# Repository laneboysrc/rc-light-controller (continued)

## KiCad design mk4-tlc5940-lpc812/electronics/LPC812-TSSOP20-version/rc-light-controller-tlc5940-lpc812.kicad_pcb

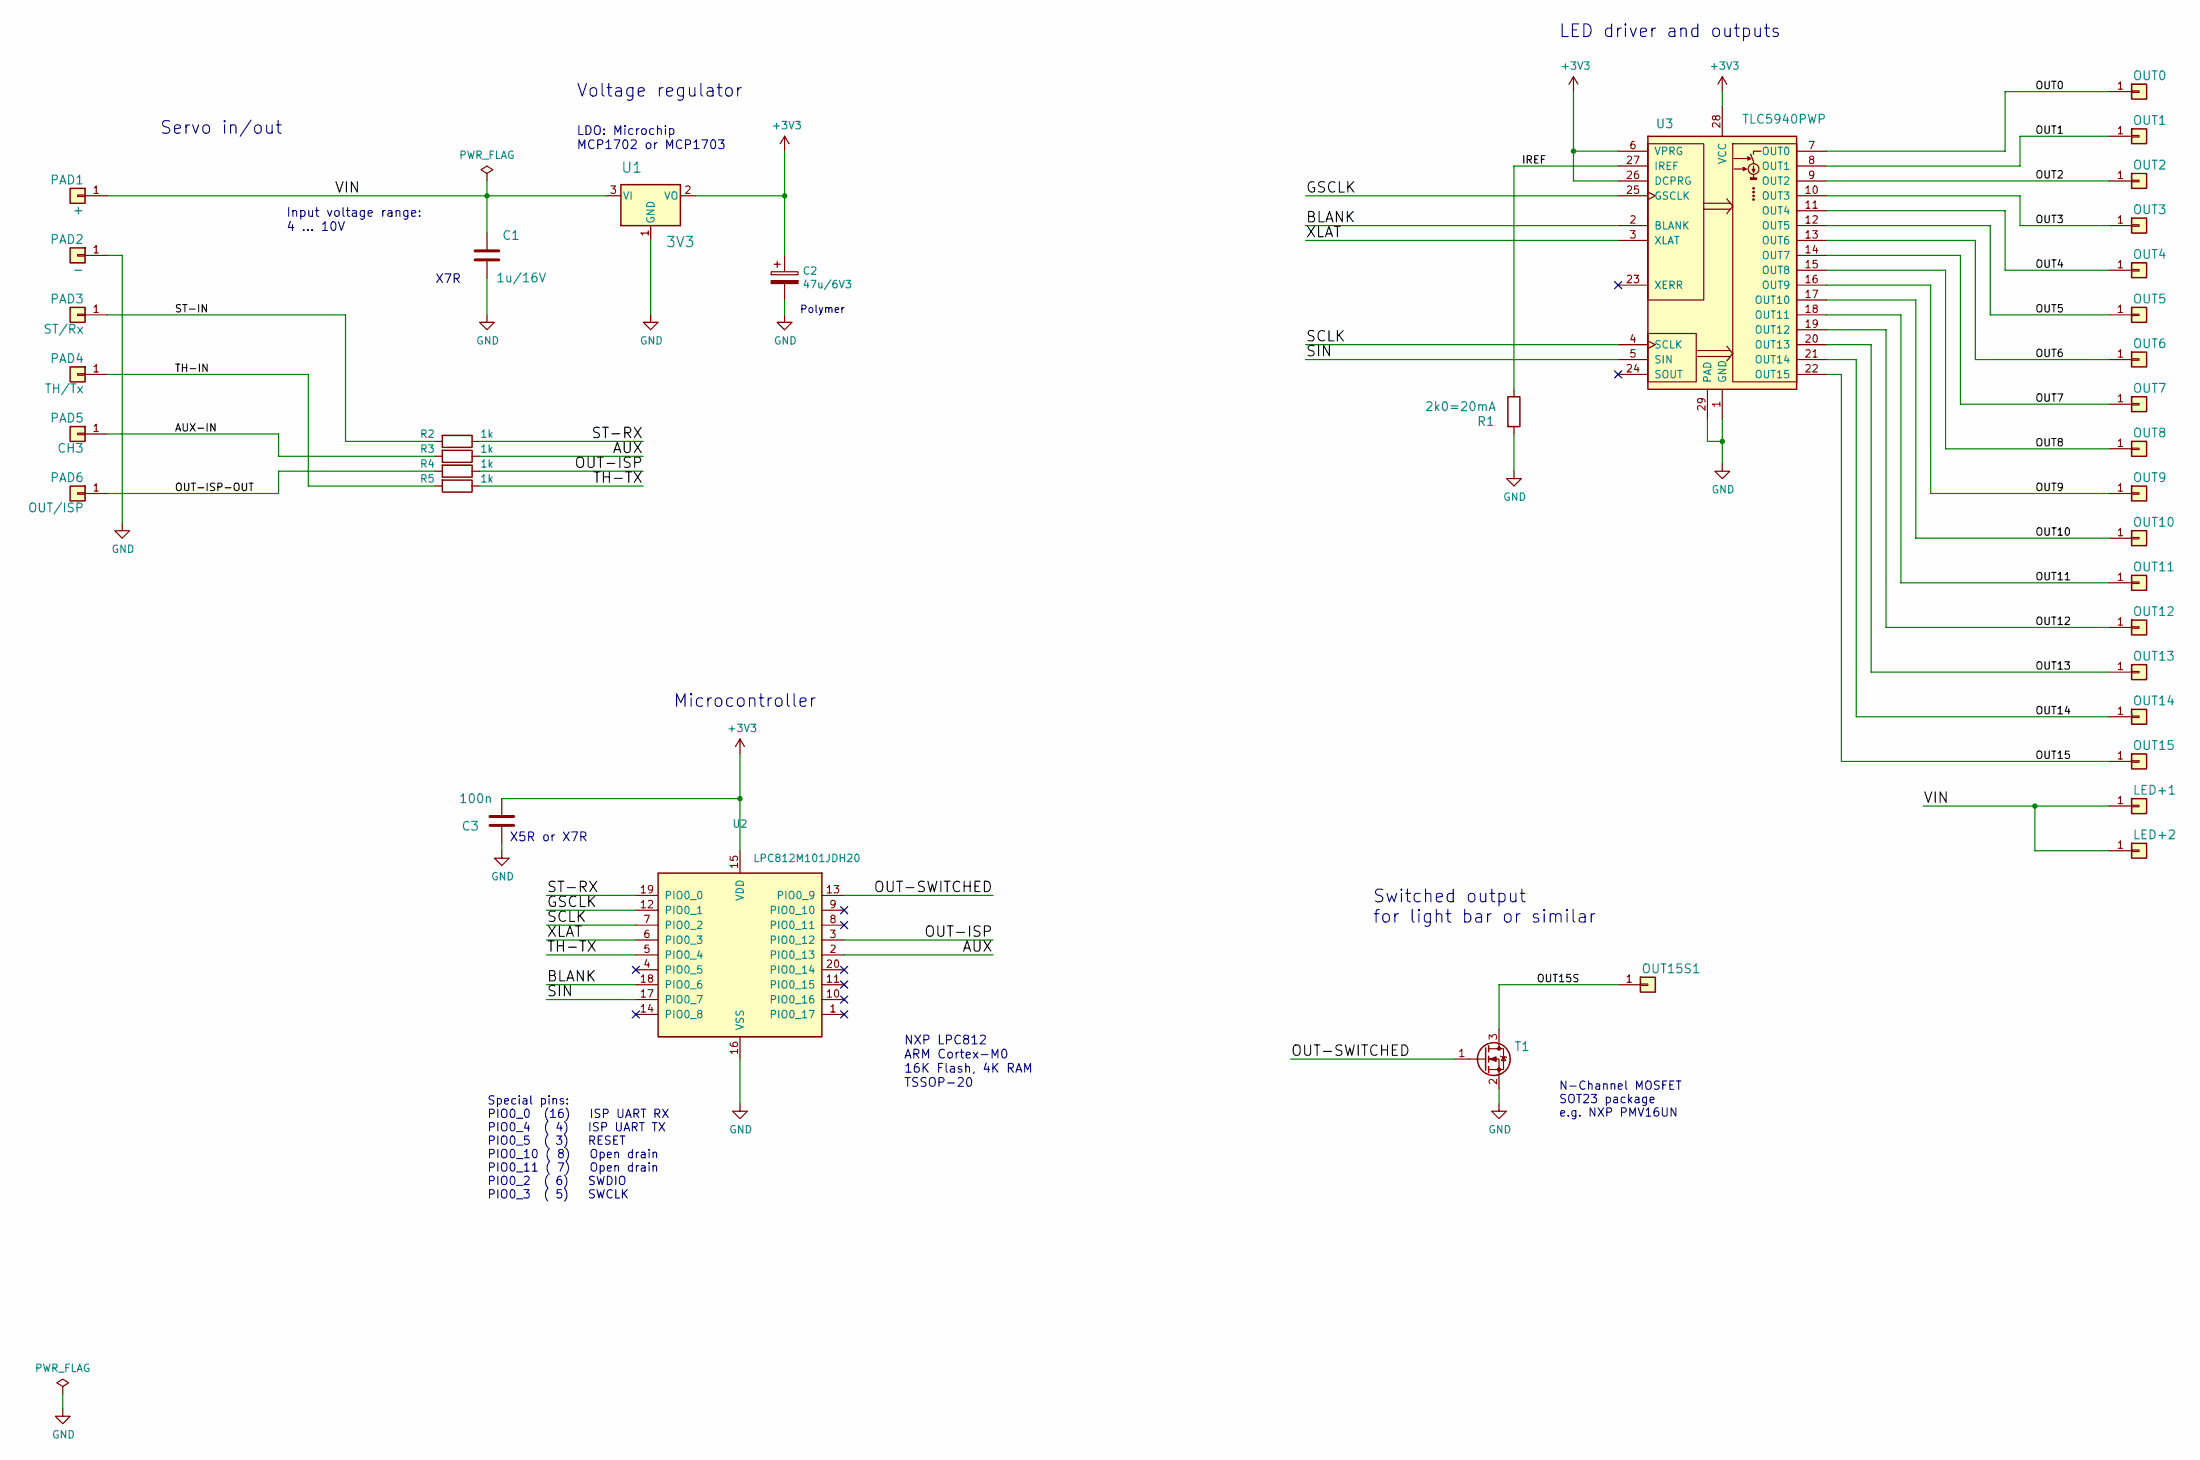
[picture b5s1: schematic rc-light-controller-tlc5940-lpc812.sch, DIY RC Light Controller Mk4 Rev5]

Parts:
C1: 1u/16V; C_0805_2012Metric
C2: 47u/6V3; C_0805_2012Metric
C3: 100n; C_0603_1608Metric
LED+1, LED+2: SMD50X100
OUT0, OUT1, OUT2, OUT3, OUT4, OUT5, OUT6, OUT7, OUT8, OUT9, OUT10, OUT11, OUT12, OUT13, OUT14, OUT15, OUT15S1: SMD50X100
PAD1: +; SMD80X120
PAD2: -; SMD80X120
PAD3: ST/Rx; SMD80X120
PAD4: TH/Tx; SMD80X120
PAD5: CH3; SMD80X120
PAD6: OUT/ISP; SMD80X120
R1: 2k0=20mA; R_0603_1608Metric
R2, R3, R4, R5: 1k; R_0603_1608Metric
T1: NMOSSOT23; SOT-23
U1: 3V3; SOT-23W
U2: LPC812M101JDH20; TSSOP-20_4.4x6.5mm_P0.65mm
U3: TLC5940PWP; SOP65P640X120-29N

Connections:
+3V3: C2.1, C3.2, U1.2 (VO), U2.15 (VDD), U3.6 (VPRG), U3.26 (DCPRG), U3.28 (VCC)
/AUX: R3.1, U2.2 (PIO0_13)
/AUX-IN: PAD5.1, R3.2
/BLANK: U2.18 (PIO0_6), U3.2 (BLANK)
/GSCLK: U2.12 (PIO0_1), U3.25 (GSCLK)
/IREF: R1.1, U3.27 (IREF)
/OUT0: OUT0.1, U3.7 (OUT0)
/OUT1: OUT1.1, U3.8 (OUT1)
/OUT2: OUT2.1, U3.9 (OUT2)
/OUT3: OUT3.1, U3.10 (OUT3)
/OUT4: OUT4.1, U3.11 (OUT4)
/OUT5: OUT5.1, U3.12 (OUT5)
/OUT6: OUT6.1, U3.13 (OUT6)
/OUT7: OUT7.1, U3.14 (OUT7)
/OUT8: OUT8.1, U3.15 (OUT8)
/OUT9: OUT9.1, U3.16 (OUT9)
/OUT10: OUT10.1, U3.17 (OUT10)
/OUT11: OUT11.1, U3.18 (OUT11)
/OUT12: OUT12.1, U3.19 (OUT12)
/OUT13: OUT13.1, U3.20 (OUT13)
/OUT14: OUT14.1, U3.21 (OUT14)
/OUT15: OUT15.1, U3.22 (OUT15)
/OUT15S: OUT15S1.1, T1.3 (D)
/OUT-ISP: R4.1, U2.3 (PIO0_12)
/OUT-ISP-OUT: PAD6.1, R4.2
/OUT-SWITCHED: T1.1 (G), U2.13 (PIO0_9)
/SCLK: U2.7 (PIO0_2), U3.4 (SCLK)
/SIN: U2.17 (PIO0_7), U3.5 (SIN)
/ST-IN: PAD3.1, R2.2
/ST-RX: R2.1, U2.19 (PIO0_0)
/TH-IN: PAD4.1, R5.2
/TH-TX: R5.1, U2.5 (PIO0_4)
/VIN: C1.1, LED+1.1, LED+2.1, PAD1.1, U1.3 (VI)
/XLAT: U2.6 (PIO0_3), U3.3 (XLAT)
GND: C1.2, C2.2, C3.1, PAD2.1, R1.2, T1.2 (S), U1.1 (GND), U2.16 (VSS), U3.1 (GND), U3.29 (PAD)

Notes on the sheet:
Special pins: PIO0_0 (16) ISP UART RX PIO0_4 ( 4) ISP UART TX PIO0_5 ( 3) RESET PIO0_10 ( 8) Open drain PIO0_11 ( 7) Open drain PIO0_2 ( 6) SWDIO PIO0_3 ( 5) SWCLK
Servo in/out
LED driver and outputs
Voltage regulator
Microcontroller
X7R
Input voltage range: 4 ... 10V
LDO: Microchip MCP1702 or MCP1703
X5R or X7R
NXP LPC812 ARM Cortex-M0 16K Flash, 4K RAM TSSOP-20
Switched output for light bar or similar
N-Channel MOSFET SOT23 package e.g. NXP PMV16UN
Polymer

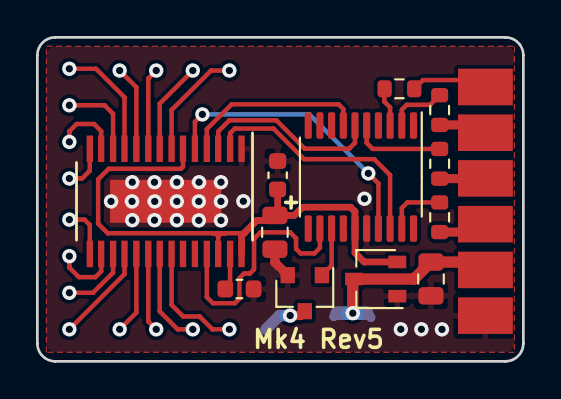
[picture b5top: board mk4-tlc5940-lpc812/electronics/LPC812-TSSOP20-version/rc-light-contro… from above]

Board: 2 copper layers, 27.0 x 18.0 mm, 37 parts (0 on the bottom side), 35 nets.

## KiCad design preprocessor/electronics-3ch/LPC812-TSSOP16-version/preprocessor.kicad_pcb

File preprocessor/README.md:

# Pre-processor

The pre-processor converts steering, throttle and AUX/CH3 signals into a single wire serial signal. By mounting the pre-processor near the receiver in the car chassis, you only need to run a standard servo extension cable to the light controller in the body shell.

This makes it very convenient when removing the body shell from the chassis: only one cable needs to be unplugged.

The pre-processor PCB also acts as "Y-cable" for steering and throttle. Use short male-to-male servo extensions to connect the pre-processor to your receiver, and plug the servo and ESC into the two extra ports on the pre-processor.

A [wiring diagram](../doc/preprocessor-wiring-diagram.pdf) explains how to connect the pre-processor, the light controller and the other electronics components in an RC car together.

The firmware for the pre-processor is the same as for the [MK4 variant](../mk4-tlc5940-lpc812/), you just have to utilize the MK4 configurator tool to generate a pre-processor firmware.

If the baud rate is configured to 38400, the pre-processor is also compatible with the MK2 and MK3 variants.

The PCB and schematics design was done in [KiCad EDA](http://kicad-pcb.org/)

3-channel Pre-Processor: [electronics-3ch/](electronics-3ch/)

5-channel Pre-Processor: [electronics-5ch/](electronics-5ch/)

5-channel Pre-Processor/switching light controller combination (4 switched LED outputs): [electronics-5ch-switching/](electronics-5ch-switching/)

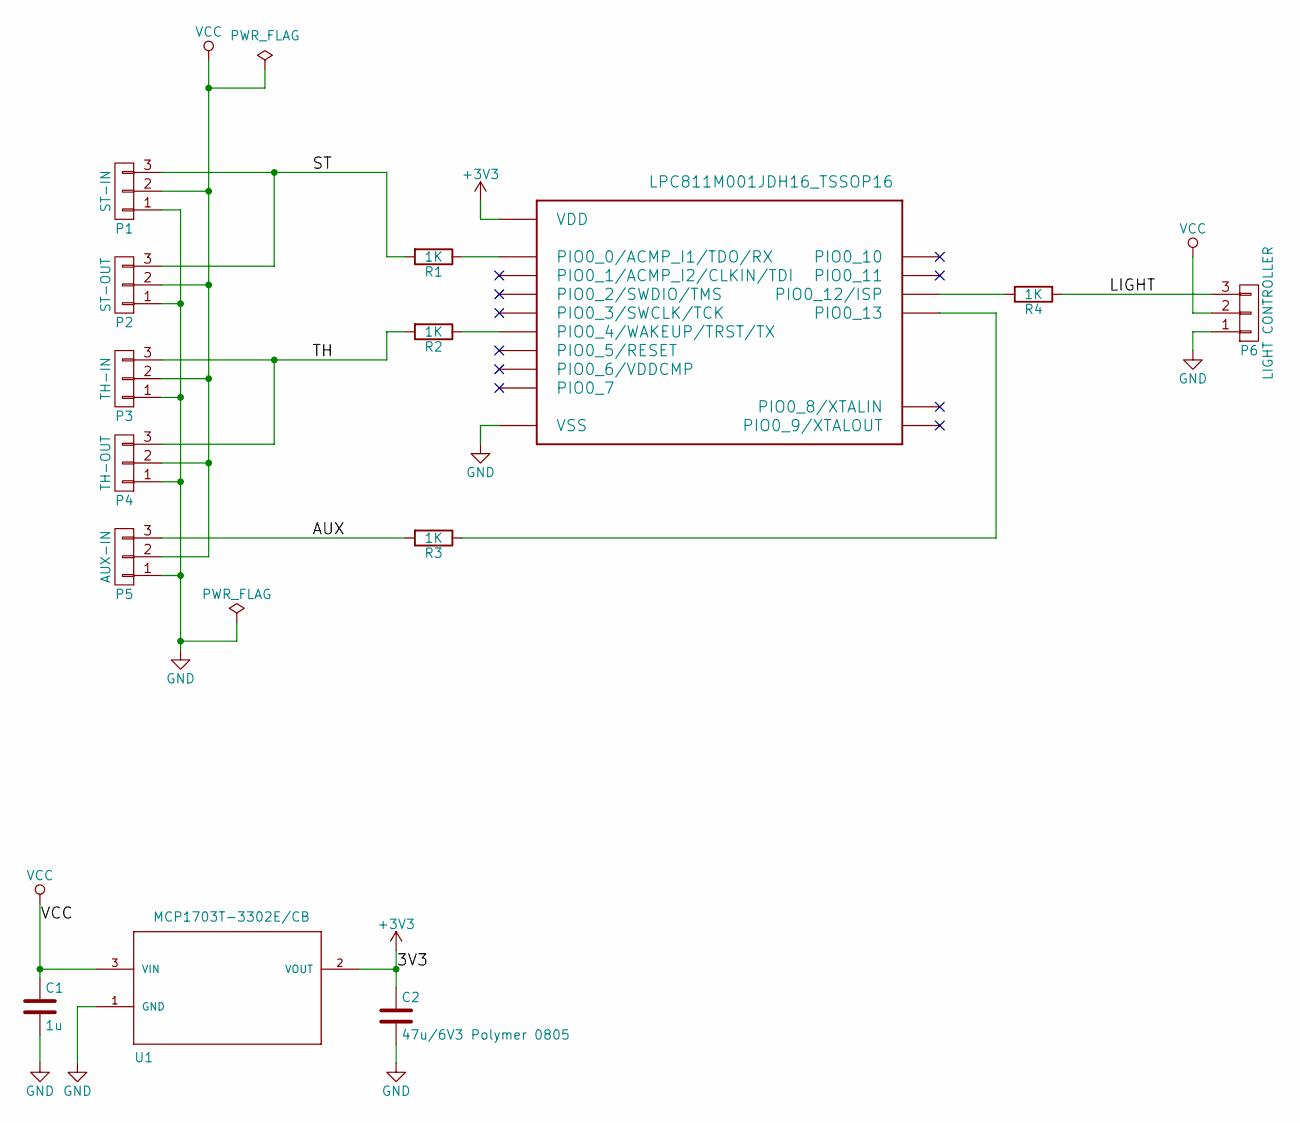
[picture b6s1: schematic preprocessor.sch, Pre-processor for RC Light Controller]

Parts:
C1: 1u; C_0805_2012Metric_Pad1.15x1.40mm_HandSolder
C2: 47u/6V3 Polymer 0805; C_0805_2012Metric_Pad1.15x1.40mm_HandSolder
P1: ST-IN; Pin_Header_Straight_1x03_Pitch2.54mm
P2: ST-OUT; Pin_Header_Straight_1x03_Pitch2.54mm
P3: TH-IN; Pin_Header_Straight_1x03_Pitch2.54mm
P4: TH-OUT; Pin_Header_Straight_1x03_Pitch2.54mm
P5: AUX-IN; Pin_Header_Straight_1x03_Pitch2.54mm
P6: LIGHT CONTROLLER; Pin_Header_Straight_1x03_Pitch2.54mm
R1, R2, R3, R4: 1K; R_0603_1608Metric_Pad1.05x0.95mm_HandSolder
U1: MCP1703T-3302E/CB; SOT-23W_Handsoldering
U2: LPC811M001JDH16_TSSOP16; TSSOP-16_4.4x5mm_P0.65mm

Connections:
+3V3: C2.1, U1.2 (VOUT), U2.12 (VDD)
/AUX: P5.3, R3.2
/LIGHT: P6.3, R4.1
/ST: P1.3, P2.3, R1.2
/TH: P3.3, P4.3, R2.2
GND: C1.2, C2.2, P1.1, P2.1, P3.1, P4.1, P5.1, P6.1, U1.1 (GND), U2.13 (VSS)
unnamed: R1.1, U2.16 (PIO0_0/ACMP_I1/TDO/RX)
unnamed: R2.1, U2.4 (PIO0_4/WAKEUP/TRST/TX)
unnamed: R3.1, U2.1 (PIO0_13)
unnamed: R4.2, U2.2 (PIO0_12/ISP)
VCC: C1.1, P1.2, P2.2, P3.2, P4.2, P5.2, P6.2, U1.3 (VIN)

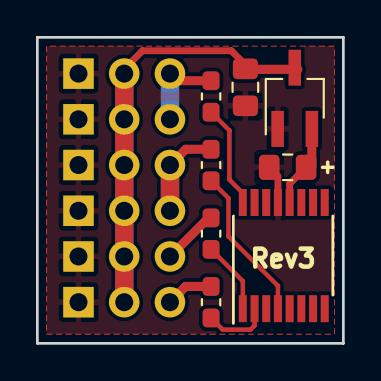
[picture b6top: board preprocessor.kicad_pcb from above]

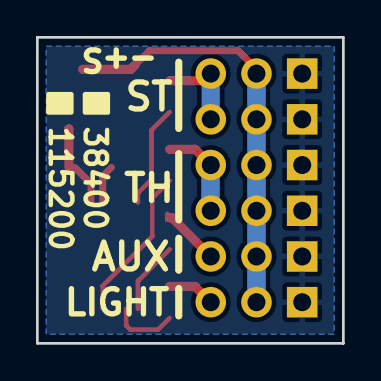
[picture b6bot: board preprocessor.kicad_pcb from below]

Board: 2 copper layers, 17.0 x 17.0 mm, 14 parts (6 on the bottom side), 11 nets.

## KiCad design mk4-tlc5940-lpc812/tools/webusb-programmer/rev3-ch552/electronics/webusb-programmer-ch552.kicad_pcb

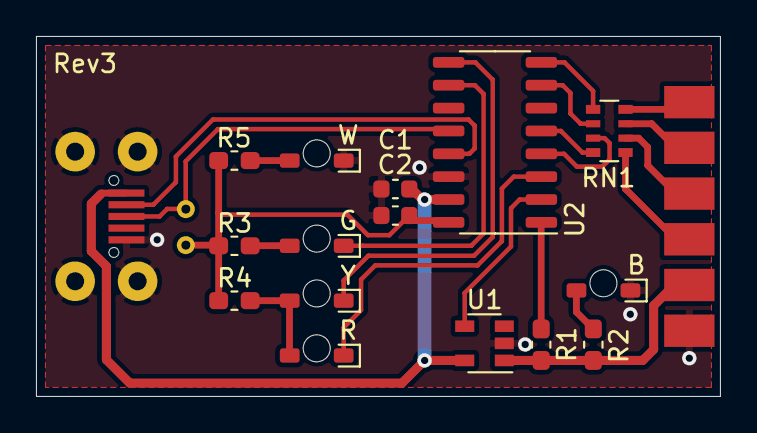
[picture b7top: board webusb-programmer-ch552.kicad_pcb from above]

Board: 2 copper layers, 38.0 x 20.0 mm, 19 parts (0 on the bottom side), 23 nets.

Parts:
C1: 1u; C_0603_1608Metric
C2: 100n; C_0603_1608Metric
D1: B; LED_1204_side_mout
D2: G; LED_1204_side_mout
D3: Y; LED_1204_side_mout
D4: R; LED_1204_side_mout
D5: W; LED_1204_side_mout
J1: Light Controller; PinHeader_1x06_P2.54mm_Flat
J2: USB_B_Micro; Mirco_USB_Type_B_LCSC_C40943
R1: 100; R_0603_1608Metric_Pad1.05x0.95mm_HandSolder
R2, R5: 1k8; R_0603_1608Metric_Pad1.05x0.95mm_HandSolder
R3: 180; R_0603_1608Metric_Pad1.05x0.95mm_HandSolder
R4: 1k2; R_0603_1608Metric_Pad1.05x0.95mm_HandSolder
RN1: 1k; R_Array_Convex_4x0603
TP1, TP2: TestPoint_THTPad_1.0x1.0mm_Drill0.5mm_nosilk
U1: STMPS2141STR; SOT-23-5
U2: CH552G; SO-16_3.9x9.9mm_P1.27mm

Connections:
+3V3: C2.1, R3.1, R4.1, R5.1, TP1.1, U2.16
+5V: C1.1, J2.1, U1.5, U2.15
/BUSY: D3.1, U2.9
/CH3: RN1.2, U2.7
/EN: U1.4, U2.2
/ERROR: D4.1, U2.3
/ISP: RN1.1, U2.8
/OK: D2.1, U2.10
/RX: RN1.3, U2.4
/SHORT: R1.2, U2.1
/TX: RN1.4, U2.5
/USB-DM: J2.2, U2.13
/USB-DP: J2.3, TP2.1, U2.12
/VLIGHT: J1.2, R1.1, R2.1, U1.1
GND: C1.2, C2.2, D1.1, D5.1, J1.1, J2.5, J2.6, U1.2, U2.14
unnamed: D1.2, R2.2
unnamed: D2.2, R3.2
unnamed: D3.2, D4.2, R4.2
unnamed: D5.2, R5.2
unnamed: J1.3, RN1.5
unnamed: J1.4, RN1.6
unnamed: J1.5, RN1.7
unnamed: J1.6, RN1.8

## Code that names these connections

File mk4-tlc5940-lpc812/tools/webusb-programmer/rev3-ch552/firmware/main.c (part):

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
#define GPIO_ADDRESS_SHORT (P3_ADDR)
#define GPIO_PIN_SHORT (2)
__sbit __at(GPIO_ADDRESS_SHORT | GPIO_PIN_SHORT) PIN_SHORT;

#define GPIO_ADDRESS_POWER (P1_ADDR)
#define GPIO_PIN_POWER (4)
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
#define GPIO_ADDRESS_ISP (P3_ADDR)
#define GPIO_PIN_ISP (0)
__sbit __at(GPIO_ADDRESS_ISP | GPIO_PIN_ISP) PIN_ISP;


// WebUSB programmer commands received via EP0 Vendor specific request
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
    // Watchdog expired: turn the power to the light controller off
    PIN_POWER = 1;
    PIN_SHORT = 0;

    // Turn the LEDs off
    LED_OK = LED_OFF;
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    LED_ERROR = LED_OFF;

    // Switch the UART TX and RX to GPIO output and set it to low, so that
    // we don't power the light controller via the ST/RX pin!
    U1REN = 0;
    TXD1 = 0;
    RXD1 = 0;
    PIN_ISP = 0;
    PIN_CH3 = 0;
}

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{
    switch (value) {
        case CMD_DUT_POWER_ON:
            PIN_SHORT = 1;
            PIN_POWER = 0;

            // Switch the TX and RX back to UART
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            PIN_POWER = 1;

            // Switch the UART TX and RX to GPIO output  and set it to low, so that
            // we don't power the light controller via the ST/RX pin!
            U1REN = 0;
            TXD1 = 0;
            RXD1 = 0;

            PIN_SHORT = 0;
            break;

        case CMD_LED_OK_ON:
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            break;

        case CMD_OUT_ISP_LOW:
            PIN_ISP = 0;
            P3_DIR_PU |= (1 << GPIO_PIN_ISP);   // Open drain output with pull-up
            break;

        case CMD_OUT_ISP_HIGH:
            PIN_ISP = 1;
            P3_DIR_PU |= (1 << GPIO_PIN_ISP);   // Open drain output with pull-up
            break;

        case CMD_OUT_ISP_TRISTATE:
            PIN_ISP = 1;
            P3_DIR_PU &= ~(1 << GPIO_PIN_ISP);  // High-impedance input mode
            break;

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    LED_ERROR = LED_OFF;

    PIN_POWER = 1;
    PIN_SHORT = 0;

    // Switch all light controller pins including UART TX and RX to low, so
    // that we don't power the light controller via the IO pins!
    PIN_ISP = 0;
    PIN_CH3 = 0;
    TXD1 = 0;
    RXD1 = 0;
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    // the ESD protection diodes of the light controller MCU -- which should
    // be fine.
    //
    // On a related note, we use the CH552 GPIO directly to short the light
    // controller power supply when off (to discharge the capacitors in the
    // light controller).
    //
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
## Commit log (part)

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2021-05-01 Fix new values when loading old configurations
2021-05-01 Make all example configurations work on latest configurator
    Main issue was labels being called "hazard", which is now
    a built-in variable by default
2021-05-08 Add updated user manual
    - New WebUSB Rev3 photo
    - Move driver info for USB-to-Serial to programming chapter
    - Add "which LEDs" info
2021-05-08 Update TODO
2021-05-09 Add product and LANE Boys RC label
2021-05-09 Rename pre-processor folders
    Instead of multi-aux, we call them 5ch as in the documentation.
    Also stream-line the folder structure of the 3ch and 5ch PP.
2021-05-09 Add 832 label
2021-05-09 Streamline gerber filenames and add schematics PDF everywhere
2021-05-10 Make ground flood go underneath LPC832
2021-05-11 Fix import of old .HEX files
2021-05-12 Add Gerber for LPC832 variants
2021-05-13 Show MCU part number in programming diagnostics
2021-05-13 Add light program that decodes multi-clicks on AUX2
2021-05-13 Improve README
2021-05-15 Adjust cut-out for the case
2021-05-20 Add "upper row is LED+" notice for Mk4P and Mk4S
2021-05-21 Fix 5ch-PP AUX2 for LPC832 variant
2021-05-22 Add German manual for 5ch-PP-S
2021-05-24 Fix PINENABLE for both LPC812 and LPC832
    v39 fixed LPC812, but 832-based Mk4P was no longer working because
    SWD pins are enabled after reset!
2021-05-24 Fix PINENABLE for LPC832l firmware v40
2021-05-26 Add light program that enables reversing lights only when main lights are on
2021-06-12 Web app for the USB-to-Serial adapter using Web Serial API
2021-06-12 Remove power status message
2021-06-12 Add WebSerial Programmer
    Now it is possible to use a standard USB-to-Serial adapter
    to program the light controller without using any 3rd party
    software.
    Works in Google Chrome, Microsoft Edge and Opera.
2021-06-27 Add wiring diagram with separte light bar battery
2021-07-04 Make NO SIGNAL and INITIALIZING mutually exclusive
2021-07-04 Update change history
2021-07-18 Add Gerber for Mk4 LPC832 version (Rev6)
2021-07-20 Add LPC832 circuit board for the Mk4S
2021-07-27 Add LPC832 PCB design for Mk4S-mini
2021-07-27 Refactor electronics version name to match everywhere
    Add LPC832 5ch-PP-S version
2021-08-10 Fix soldermask settings
2021-08-29 Fix shelf queen mode
    Issue with the new diagnstics taking place even when
    shelf queen mode is active.
2021-09-19 Add diagram with separate power supply for LEDs
2021-09-19 Update schematics to reflect green LED being low brightness
2021-09-19 Update with latest configurator
2021-10-02 Fix light program (hazard is now a global variable)
2021-10-02 Add light program that disables servo output at light switch positions
2021-10-07 Fix old light programs use of 'hazard' (now a reseved word)
2021-11-01 Add WebUSB Revision 4 draft, based on motor driver as power switch
2021-11-02 Rename files and tweak the layout around the motor driver
2021-11-03 Improve naming of project specific schematics component library
2021-11-04 Fix setting of SMOD for fast baudrate mode
2021-11-05 Change version number for Rev4 WebUSB version
2021-11-12 Add i-Bus test configurator
2021-11-13 Improve WebUSB documentation; move USB-to-Serial to appendix
2021-11-14 Update i-Bus test version with reduced diagnostics
2021-11-15 Remove unused ignore entries
2021-11-22 Save a few bytes by combining indicator printf calls
2021-11-22 Make print_indicator_state static
2021-11-22 Make on_off_function generic to prepare for shelf queen via AUX
2021-11-23 Light programs can now control the shelf queen mode
2021-11-23 Add WebUSB Rev 4 Gerber
2021-11-23 Improve hazard switching
2021-11-24 Disable car functions in shelf queen mode
2021-11-24 Add info regarding shelf queen mode from light program
2021-11-26 Basic LED name editing works
2021-11-26 Add support for LED names to the light program assembler
2021-11-26 Make led names assemble
2021-11-26 Add tooltip to LED name
2021-11-26 Add history
2021-11-26 Add support for LED names in LED configuration and light programs
2021-11-27 Drag configuration files from file manager to the Configurator window
2021-11-27 Update with configurator supporting drag-and-drop
2021-11-27 Add toast when configuration loaded
2021-11-27 Show toast when loading a configuration
2021-11-27 Remove more obsolete files; fix broken links and clarify things
2021-12-03 Add PCB thickness to Gerber filename
2021-12-07 i-Bus implementation done
2021-12-07 Automatic protocol selection now working
2021-12-07 Add info for i-Bus operating mode
2021-12-07 Make servo, pre-processor and i-bus reader conditionally compilable
2021-12-07 Add i-Bus example data from an actual receiver and fix i-Bus decoder
2021-12-08 Update i-Bus version (merged latest master)
2021-12-18 Update TODO list
2021-12-20 Fix all leds if no LED declared
    If no LED is defined, but an assinment was made to "all leds",
    then an error message was shown without any information what
    the issue was.
    Example:
    run always
    all leds = 100
2021-12-21 Increase firmware version to 50 as first i-Bus version
2021-12-22 Update i-Bus documentation and TODO list
2021-12-22 Add offset for AUX channel mapping in i-Bus mode
2021-12-23 Implement i-Bus channel offset for AUX
2021-12-23 Focus programming button when connecting WebUSB in programming page
2021-12-25 Add LPC832 support
2021-12-28 Add i-Bus to documentation
2021-12-28 Update with latest configurator supporting i-Bus
2022-01-09 Add more info about S.Bus and add packet decoder in Python
2022-01-12 Improve the silkscreen
2022-01-12 Move resistor network and improve tracks
2022-01-12 Add Rev3 gerbers
2022-01-15 Add BOM for WebUSB Programmer Rev4
2022-01-19 Add statement regarding one LED per output (or two in series)
    Suggestion from light controller user!
2022-01-27 Change SBUS inverter MOSFET and pullup after testing
2022-01-29 Cleanup and improvements
2022-01-29 Clean-up and restore config
2022-01-29 Add skeleton for WebSerial based S-Bus simulator
2022-01-29 Improve documentation for S.Bus simulator
2022-01-29 SBUS now working!
2022-01-30 Add a blank favicon directly into the HTML
2022-01-30 Improve grammar; add history entry for S.Bus
2022-02-02 Add instructions for S.Bus support
2022-03-22 Add interior light when car is in neutral light program
2022-03-24 Make C1 on WebUSB 10uF to combat voltage drop when light controller is turned on
2022-04-10 Release S.Bus support
2022-05-03 Improve schematics and layout
2022-05-05 Add Gerber for Mk4 Rev7 with S.Bus support
2022-05-07 Add light program that switches certain lights on AUX2
2022-05-14 Make Mk4 Rev7 S.Bus case fit
2022-05-14 Support channels 3..16 when using S.Bus
2022-06-11 Add light program for hazard indicator on dashboard
2022-06-12 Add S.Bus for Mk4
2022-06-16 Add Mk4 Rev7 images
2022-06-17 Add Mk4 Rev 7 documentation with S.Bus support
2022-06-25 Save a few bytes by using int as loop counter
2022-06-25 Fix HEX can not be saved
2022-06-27 Add UI to disable local push button in 5chPP/i-Bus/S.Bus mode
2022-07-02 Update Mk4 offline package with latest configurator
2022-07-14 Use RXPOL to invert S.Bus UART instead of hardware inverter
2022-07-14 Output correct MCU type in diagnostics
    Refactor from a flag to the variable mcu_type
2022-07-14 WebUSB and WebSerial work on file: protocol now
2022-07-15 Use LPC81x_ISP.py tool with .hex as .bin does not work on Python3
2022-07-15 Update WebUSB and WebSerial stand-alone programmers
2022-07-16 Update configurator with version that works on file: protocol
2022-07-18 Add UI for reading of firmware, read into .hex file
2022-07-18 Describe how the read function works around the WebUSB programmer bug
2022-07-18 Add read HEX function to programmer.html for WebUSB
2022-07-22 Fix loading of same .hex file
2022-08-21 Add diagrams for slave with servo reader
2022-08-29 Improve LED value editing
2022-08-31 Add statement that WebUSB requires Windows 8.1 or newer
2022-11-06 Improve description for Baudrate
2022-11-23 Fix Slave when running at 100000 BAUD
    Issue: the slave must not invert the Rx pin! Only when processing
    S-Bus input do we want to invert the Rx pin.
2022-11-23 Fix Slave with 100000 BAUD
2022-12-31 Fix light program name
2023-02-08 Rename wiring diagrams
2023-02-08 Start to get WS2812 working
2023-02-09 Update WS2811 implememtation, works with WS2812B for now
2023-02-10 Add timing for WS2812B and WS2811
2023-02-15 Make WS2811 work
2023-02-15 Use lookup table and transmiter 16 bits in one go
2023-03-03 Fix AUX values being wrong after starting simulator
    The sliders were kept in their position between invocations,
    but the underlying simulator was always reset to 0, so initially
    the values sent to the light controller did not match the
    slider values until a slider is moved.
2023-03-03 Fix AUX values being wrong after starting simulator
2023-04-30 New lpc81x_isp version that supports LPC824
2023-05-28 WS2811 now works on OUT15S with 470R pull-up
    We basically use the transistor as level shifter, but need to
    deal with an inverted signal
2023-06-09 Code now works with WS2811 and the buffer on OUT/ISP
2023-06-09 Add WS281x info and TODO
2023-06-09 Start on disassembler
2023-06-10 Light programs now work, including assembler/disasm/configurator
2023-06-10 Implement ws2811 output options logic
2023-06-12 Rename configurator output file
2023-06-13 Add documentation, Fix data=0xff/fe issue
2023-06-14 Add documentation skeleton
2023-06-16 Add CSS trick for margin
2023-06-16 Reduce code size and add 3 more AUX channels
    AUX4..6 can only be used in light programs
2023-06-16 Add 4 more AUX to simulator and update docs
2023-06-17 Improve documentation, add images
2023-06-18 Add US style school bus red and yellow flashing light
2023-06-18 Add support for AUX4..6 for i-Bus and S.Bus
2023-06-18 Add WS281x documentation and Configurator
2023-06-18 Add PDF and update README
2023-06-20 Add -fshort-enums to pack enums
    This seems to be already the case anyway, but just in case...
2023-06-21 Add DMA code, not tested
2023-06-22 WS281x driver uses DMA to offload the MCU
2023-08-26 Fix Webserial Programmer
2023-09-03 Add WebUSB Rev5 PCB with USB Type C connector
2023-09-07 Move obsolete stuff to branch named 'obsolete'
2023-10-29 Re-add tools
2023-11-06 Add 5ch PP flash diagram
2023-11-07 Start on advanced 3ch AUX configuration
2023-11-08 Make Advanced 3 channel AUX work
2023-11-08 Increment firmware version number
2023-11-08 Port more tools to Python3
2023-11-09 Fix 3ch PP not setting multi-aux flag despite outputing full packet
2023-11-09 Pre-processor always outputs 5 channels. Advanved CH3 settings
2023-11-16 Add files for Pre-processor programming
2023-12-29 Fix servo setup number of clicks is 8, not 7
2024-01-05 Add configuration that fits TRX4M
2024-01-08 Confirmed working configuration for TRX4m (finally...)
2024-01-09 WS281x: output master LEDs too
2024-03-29 Shrink screw holes for a better fit
2024-03-29 Add light program that turns off lights in neutral, restores when driving
2024-09-09 Fix LED names defined in the table were only working in the first Light program
2024-11-05 Remove WebUSB rev 4 (moved to 'obsolete' branch)
2024-11-06 Start on WebUSB rev6 hardware
2024-12-03 WebUSB rev 6 for production
2025-01-12 Add servo output on Slave controlled by light program on Master
2025-01-12 Update Mk4P README
2025-01-13 Port Mk4S to Kicad6; Improve silkscreen for Mk4P and Mk4S
2025-01-13 Fix layout and pass DRC
2025-01-22 Remove WebUSB Rev 5
2025-01-22 Improve file names, BOM and gerbers
2025-01-30 Add light program for random servo movement
2025-02-04 Make multi-function control use advanced settings two-position switch hysteresis
2025-05-01 Add servo out pulse to configurator
2025-05-01 Add configuable servo output range to firmware
2025-05-01 Add servo out pulse configuration to advanced settings
2025-05-22 Remove files that are not required
2025-05-22 Force Slave output to OUT/ISP on slave
2025-05-22 Implement LED table, seems to work now
2025-05-22 Add multi-slave that can drive up to 3 slaves (64 LEDs)
2025-06-09 Multislave: fix LED features not working for Slave 2 and 3
2025-06-09 Multislave: fix firmware version in history
2025-07-27 Light programs run up to 30 (not 50) statements before suspension
